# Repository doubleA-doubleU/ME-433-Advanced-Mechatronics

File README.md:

# ME-433-Advanced-Mechatronics

This repo contains all of my files associated with the homework/projects for ME 433: Advanced Mechatronics, Spring 2017.
Aaron Weatherly, Graduate Student, Northwestern University

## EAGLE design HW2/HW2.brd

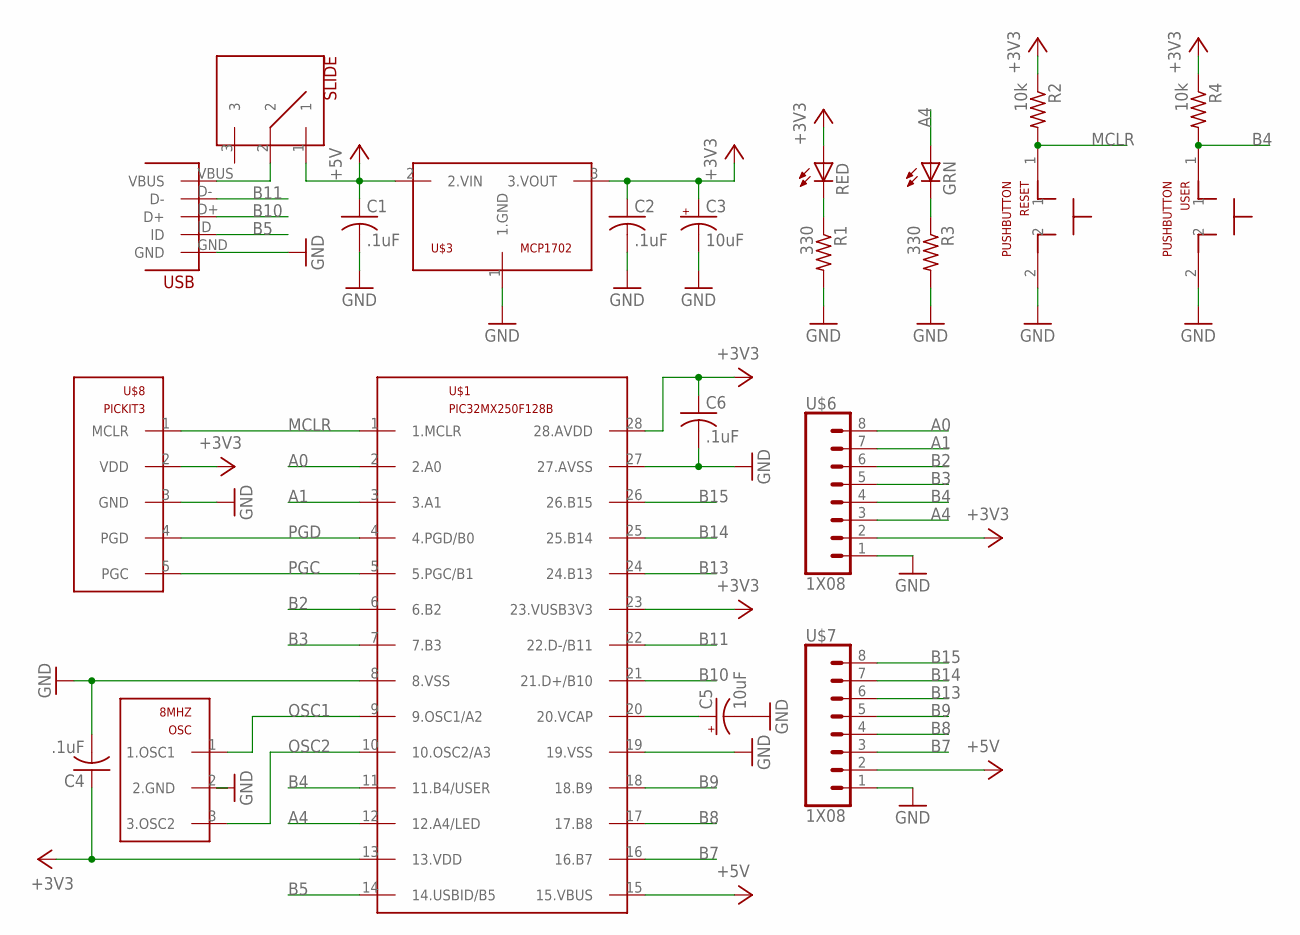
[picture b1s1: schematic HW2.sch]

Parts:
8MHZ: OSC
C1, C2, C4, C6: .1uF; C025-025X050
C3, C5: 10uF; B45181B
GRN: LED3MM
R1, R3: 330; 0207/10
R2, R4: 10k; 0207/10
RED: LED3MM
RESET: PUSHBUTTON
SLIDE: SLIDESWITCH
U$1: PIC32MX250F128B; DIL28-3
U$3: MCP1702; TO92
U$5: MINIUSB; USB-MB-H
U$6, U$7: 1X08; CONN_08
U$8: PICKIT3
USER: PUSHBUTTON

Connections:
+3V3: C2.1, C3.+, C4.1, C6.1, R2.1, R4.1, RED.A, U$1.13 (13.VDD), U$1.23 (23.VUSB3V3), U$1.28 (28.AVDD), U$3.3 (3.VOUT), U$6.2, U$8.2 (VDD)
+5V: C1.1, SLIDE.1, U$1.15 (15.VBUS), U$3.2 (2.VIN), U$7.2
A0: U$1.2 (2.A0), U$6.8
A1: U$1.3 (3.A1), U$6.7
A4: GRN.A, U$1.12 (12.A4/LED), U$6.3
B2: U$1.6 (6.B2), U$6.6
B3: U$1.7 (7.B3), U$6.5
B4: R4.2, U$1.11 (11.B4/USER), U$6.4, USER.1
B5: U$1.14 (14.USBID/B5), U$5.ID
B7: U$1.16 (16.B7), U$7.3
B8: U$1.17 (17.B8), U$7.4
B9: U$1.18 (18.B9), U$7.5
B10: U$1.21 (21.D+/B10), U$5.D+
B11: U$1.22 (22.D-/B11), U$5.D-
B13: U$1.24 (24.B13), U$7.6
B14: U$1.25 (25.B14), U$7.7
B15: U$1.26 (26.B15), U$7.8
GND: 8MHZ.2 (2.GND), C1.2, C2.2, C3.-, C4.2, C5.-, C6.2, R1.2, R3.2, RESET.2, U$1.8 (8.VSS), U$1.19 (19.VSS), U$1.27 (27.AVSS), U$3.1 (1.GND), U$5.GND, U$6.1, U$7.1, U$8.3 (GND), USER.2
MCLR: R2.2, RESET.1, U$1.1 (1.MCLR), U$8.1 (MCLR)
unnamed: R1.1, RED.K (C)
unnamed: GRN.K (C), R3.1
OSC1: 8MHZ.1 (1.OSC1), U$1.9 (9.OSC1/A2)
OSC2: 8MHZ.3 (3.OSC2), U$1.10 (10.OSC2/A3)
PGC: U$1.5 (5.PGC/B1), U$8.5 (PGC)
PGD: U$1.4 (4.PGD/B0), U$8.4 (PGD)
VBUS: SLIDE.2, U$5.VBUS
VCAP: C5.+, U$1.20 (20.VCAP)

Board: 2 copper layers, 22 parts (0 on the bottom side), 27 nets, no tracks yet.

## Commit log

2017-03-29 Circuit Diagram
    Includes connections for all essential power, programming, and debugging
    pins.
2017-03-29 Breadboard
    Includes connections for all essential power, programming, and debugging
    pins.
2017-03-29 Code template
    To be modified as needed
2017-03-29 Voltage Regulator
    Screenshots of clean and oscillatory output of the MCP1702 voltage
    regulator.
2017-03-29 MPLABX Project Files
    Initial upload
2017-03-30 Final Code
    HW1 Final Submission
2017-04-04 HW2
    PCB Schematic and Library (and an incomplete .brd file) . Also, an
    updated circuit diagram.
2017-04-07 HW3
    Final PCB design
2017-04-10 HW1 updated makefile
    Upgraded XC32 compiler to version 1.43
2017-04-10 HW4
    MCP4902 DAC
2017-04-12 HW5
    Initial upload
2017-04-13 HW5
    I2C Pin Expansion
2017-04-13 HW5
    Demo video
2017-04-17 HW6
    LCD Hello World
2017-04-20 HW7
    Print accelerometer data to LCD screen
2017-04-22 HW8
    Using Harmony to redo HW1 and HW7
2017-05-02 HW10
2017-05-02 HW11
2017-05-06 HW12
2017-05-09 HW13
2017-05-11 HW14
2017-05-18 HW15
2017-05-18 HW16
2017-05-23 HW17
2017-05-28 HW18
2017-05-28 HW19
2017-05-28 HW20
2017-05-31 HW14
    Updated seekbar values
2017-10-26 Updated vive tracking and path color
